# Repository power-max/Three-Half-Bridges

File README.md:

# Three Half Bridges
Three Half Bridges project is intended to be a universal(ish) module for use in larger power conversion and motor control systems. This PCB aims to create a reasonably universal half bridge driver that can be used for medium to high power (100W to 1kW) electrical systems, such as power converters (buck converter, forward converter, LC or LLC converter, etc) motor drivers, etc. As such it is fairly bare-bones and additional components may need to be added external to this PCB for a particular system.

Digital isolator ICs are used for providing isolated gate drive signals and pretty much any generic low-side gate driver can be used for the actual gate driver ICs. I found some cheapies on LCSC for less than a dollar that claim 4A source and sink per channel, and each channel is paralell so in theory 8A source and sink is achievable. Note that there is no logic to prevent shoot-through, as the user inputs each high and low switch independently. Use a TL494 style flip flop based pulse steering network or my Dead Time Insertion PCB to implement this logic from a single ended square wave.

Notes:
The end-user is responsible for selecting the exact componts used for this PCB design. (i.e. MOSFET or IGBT choice, choice of gate driver IC, value of capcitors, etc)

Licensed under the MIT License (https://mit-license.org/)

I was really drunk when I wrote this. Please consider buyin gm e more beerrs so I caan contune edevelopment thnaks!

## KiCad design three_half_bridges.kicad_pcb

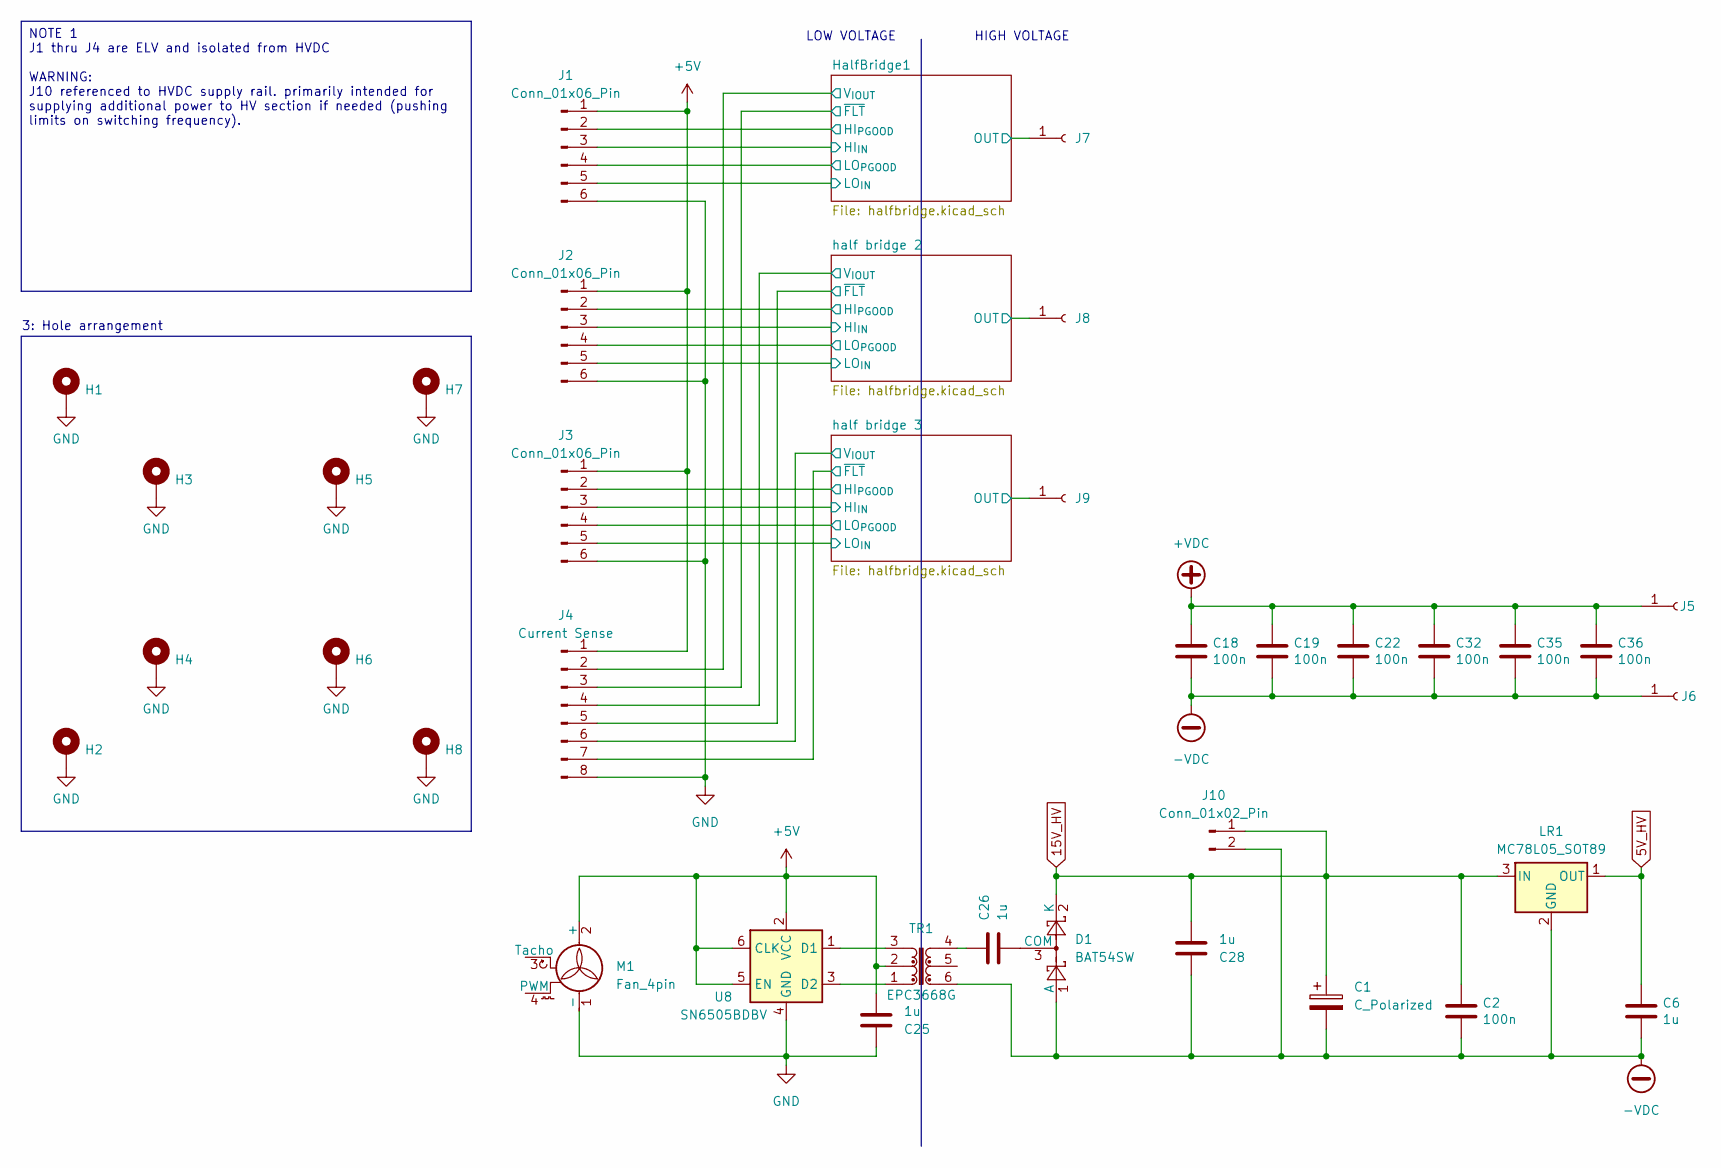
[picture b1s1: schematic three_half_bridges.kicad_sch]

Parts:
C1: C_Polarized; CP_EIA-6032-20_AVX-F
C2: 100n; C_0805_2012Metric
C6: 1u; C_0805_2012Metric
C18, C19, C22, C32, C35, C36: 100n; C_1812_4532Metric
C25, C26, C28: 1u; C_0603_1608Metric
D1: BAT54SW; SOT-323_SC-70
H1, H2, H7, H8: MountingHole_Pad; MountingHole_3.2mm_M3_Pad_Via
H3, H4, H5, H6: MountingHole_Pad; MountingHole_5.5mm_Pad_Via
J1, J2, J3: Conn_01x06_Pin; Molex_PicoBlade_53047-0610_1x06_P1.25mm_Vertical
J4: Current Sense; Molex_PicoBlade_53047-0810_1x08_P1.25mm_Vertical
J5, J6, J7, J8, J9: Conn_01x01_Socket; AMT0450028DB0000G
J10: Conn_01x02_Pin; JST_XH_B2B-XH-A_1x02_P2.50mm_Vertical
LR1: MC78L05_SOT89; SOT-89-3
M1: Fan_4pin; Molex_KK-254_AE-6410-04A_1x04_P2.54mm_Vertical
TR1: EPC3668G; Pulse_PA2004NL
U8: SN6505BDBV; SOT-23-6

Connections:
5V_HV: C6.2, LR1.1 (OUT); also elsewhere on the board
15V_HV: C1.1, C2.2, C28.2, D1.2 (K), J10.1, LR1.3 (IN); also elsewhere on the board
+5V: C25.2, J1.1, J2.1, J3.1, J4.1, M1.2 (+), TR1.2, U8.2 (VCC), U8.5 (EN), U8.6 (CLK); also elsewhere on the board
+VDC: C18.2, C19.2, C22.2, C32.2, C35.2, C36.2, J5.1; also elsewhere on the board
-VDC: C1.2, C2.1, C6.1, C18.1, C19.1, C22.1, C28.1, C32.1, C35.1, C36.1, D1.1 (A), J6.1, J10.2, LR1.2 (GND), TR1.6; also elsewhere on the board
/half bridge 1/HI_{IN}: J1.3; also elsewhere on the board
/half bridge 1/HI_{PGOOD}: J1.2; also elsewhere on the board
/half bridge 1/LO_{IN}: J1.5; also elsewhere on the board
/half bridge 1/LO_{PGOOD}: J1.4; also elsewhere on the board
/half bridge 1/OUT: J7.1; also elsewhere on the board
/half bridge 1/V_{IOUT}: J4.2; also elsewhere on the board
/half bridge 1/~FLT: J4.3; also elsewhere on the board
/half bridge 2/HI_{IN}: J2.3; also elsewhere on the board
/half bridge 2/HI_{PGOOD}: J2.2; also elsewhere on the board
/half bridge 2/LO_{IN}: J2.5; also elsewhere on the board
/half bridge 2/LO_{PGOOD}: J2.4; also elsewhere on the board
/half bridge 2/OUT: J8.1; also elsewhere on the board
/half bridge 2/V_{IOUT}: J4.4; also elsewhere on the board
/half bridge 2/~FLT: J4.5; also elsewhere on the board
/half bridge 3/HI_{IN}: J3.3; also elsewhere on the board
/half bridge 3/HI_{PGOOD}: J3.2; also elsewhere on the board
/half bridge 3/LO_{IN}: J3.5; also elsewhere on the board
/half bridge 3/LO_{PGOOD}: J3.4; also elsewhere on the board
/half bridge 3/OUT: J9.1; also elsewhere on the board
/half bridge 3/V_{IOUT}: J4.6; also elsewhere on the board
/half bridge 3/~FLT: J4.7; also elsewhere on the board
GND: C25.1, H1.1, H2.1, H3.1, H4.1, H5.1, H6.1, H7.1, H8.1, J1.6, J2.6, J3.6, J4.8, M1.1 (-), U8.4 (GND); also elsewhere on the board
unnamed: C26.1, TR1.4
unnamed: C26.2, D1.3 (COM)
unnamed: TR1.3, U8.1 (D1)
unnamed: TR1.1, U8.3 (D2)

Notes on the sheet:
LOW VOLTAGE
HIGH VOLTAGE
3: Hole arrangement
NOTE 1 J1 thru J4 are ELV and isolated from HVDC WARNING: J10 referenced to HVDC supply rail. primarily intended for supplying additional power to HV section if needed (pushing limits on switching frequency).

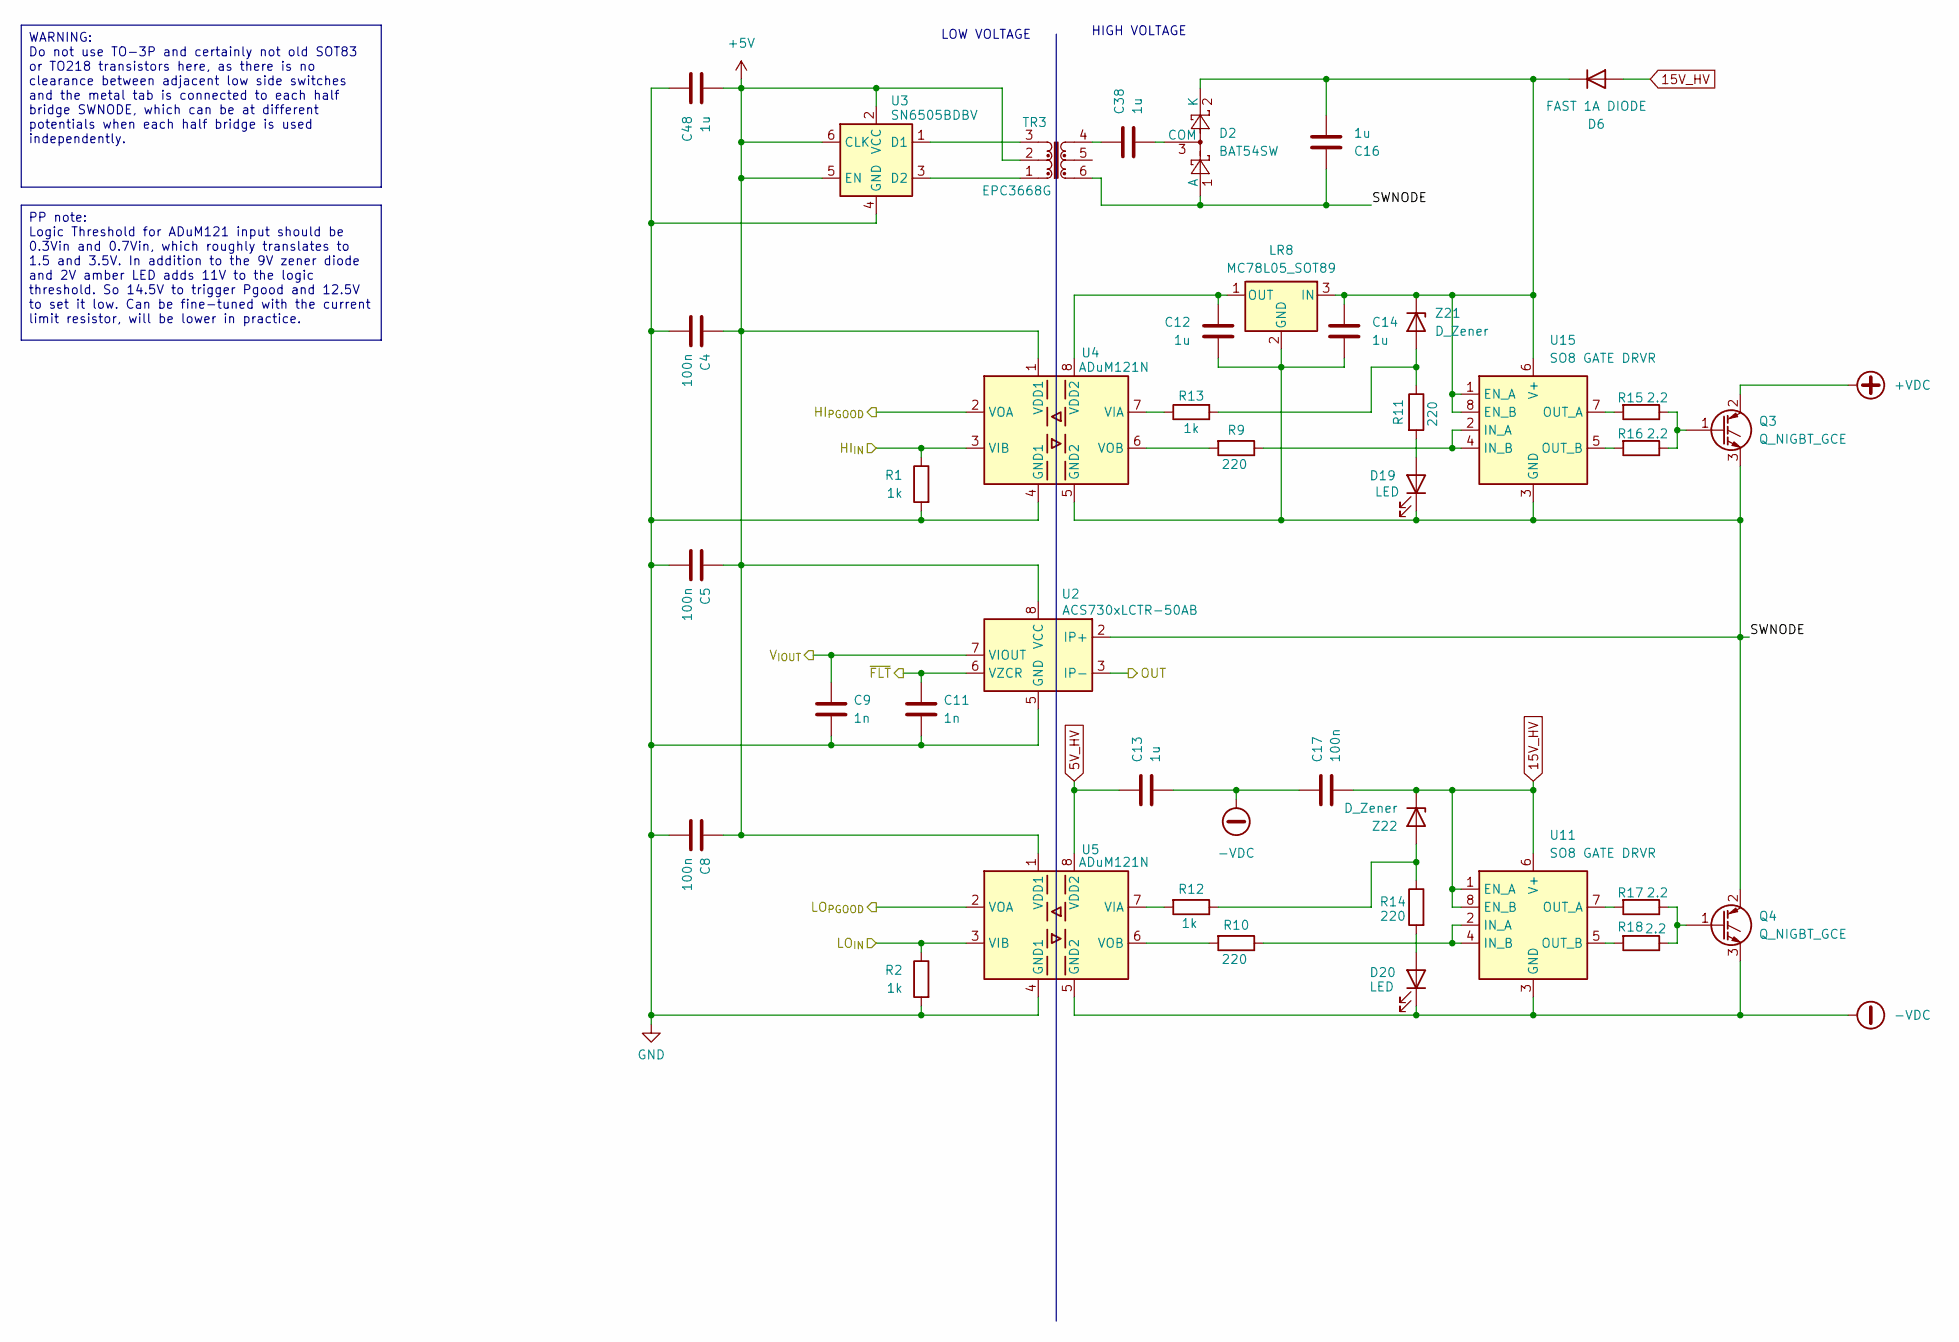
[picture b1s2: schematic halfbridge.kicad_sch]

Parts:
C4, C5, C8, C17: 100n; C_0603_1608Metric
C9, C11: 1n; C_0603_1608Metric
C12, C13, C14, C16, C38, C48: 1u; C_0603_1608Metric
D2: BAT54SW; SOT-323_SC-70
D6: FAST 1A DIODE; D_SOD-128
D19, D20: LED; LED_0805_2012Metric
LR8: MC78L05_SOT89; SOT-89-3
Q3, Q4: Q_NIGBT_GCE; TO-247-3-Nogloryhole_Horizontal_TabUp
R1, R2, R12, R13: 1k; R_0603_1608Metric
R9, R10, R11, R14: 220; R_0603_1608Metric
R15, R16, R17, R18: 2.2; R_1206_3216Metric
TR3: EPC3668G; Pulse_PA2004NL
U2: ACS730xLCTR-50AB; SOIC-8_3.9x4.9mm_P1.27mm
U3: SN6505BDBV; SOT-23-6
U4, U5: ADuM121N; SOIC-8_3.9x4.9mm_P1.27mm
U11, U15: SO8 GATE DRVR; SO-8_3.9x4.9mm_P1.27mm
Z21, Z22: D_Zener; D_SOD-123

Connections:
5V_HV: C13.1, U5.8 (VDD2); also elsewhere on the board
15V_HV: C17.2, D6.2 (A), U11.1 (EN_A), U11.6 (V+), U11.8 (EN_B), Z22.1 (K); also elsewhere on the board
+5V: C4.1, C5.1, C8.1, C48.2, TR3.2, U2.8 (VCC), U3.2 (VCC), U3.5 (EN), U3.6 (CLK), U4.1 (VDD1), U5.1 (VDD1); also elsewhere on the board
+VDC: Q3.2 (C); also elsewhere on the board
-VDC: C13.2, C17.1, D20.1 (K), Q4.3 (E), U5.5 (GND2), U11.3 (GND); also elsewhere on the board
/half bridge 2/HI_{IN}: R1.1, U4.3 (VIB); also elsewhere on the board
/half bridge 2/HI_{PGOOD}: U4.2 (VOA); also elsewhere on the board
/half bridge 2/LO_{IN}: R2.1, U5.3 (VIB); also elsewhere on the board
/half bridge 2/LO_{PGOOD}: U5.2 (VOA); also elsewhere on the board
/half bridge 2/OUT: U2.3 (IP-), U2.4 (IP-); also elsewhere on the board
/half bridge 2/SWNODE: C12.2, C14.2, C16.1, D2.1 (A), D19.1 (K), LR8.2 (GND), Q3.3 (E), Q4.2 (C), TR3.6, U2.1 (IP+), U2.2 (IP+), U4.5 (GND2), U15.3 (GND)
/half bridge 2/V_{IOUT}: C9.1, U2.7 (VIOUT); also elsewhere on the board
/half bridge 2/~FLT: C11.1, U2.6 (VZCR); also elsewhere on the board
GND: C4.2, C5.2, C8.2, C9.2, C11.2, C48.1, R1.2, R2.2, U2.5 (GND), U3.4 (GND), U4.4 (GND1), U5.4 (GND1); also elsewhere on the board
unnamed: C38.1, TR3.4
unnamed: C38.2, D2.3 (COM)
unnamed: C14.1, C16.2, D2.2 (K), D6.1 (K), LR8.3 (IN), U15.1 (EN_A), U15.6 (V+), U15.8 (EN_B), Z21.1 (K)
unnamed: D19.2 (A), R11.2
unnamed: D20.2 (A), R14.2
unnamed: C12.1, LR8.1 (OUT), U4.8 (VDD2)
unnamed: Q3.1 (G), R15.1, R16.1
unnamed: Q4.1 (G), R17.1, R18.1
unnamed: TR3.3, U3.1 (D1)
unnamed: TR3.1, U3.3 (D2)
unnamed: R13.1, U4.7 (VIA)
unnamed: R9.2, U4.6 (VOB)
unnamed: R12.2, U5.7 (VIA)
unnamed: R10.2, U5.6 (VOB)
unnamed: R10.1, U11.2 (IN_A), U11.4 (IN_B)
unnamed: R17.2, U11.7 (OUT_A)
unnamed: R18.2, U11.5 (OUT_B)
unnamed: R9.1, U15.2 (IN_A), U15.4 (IN_B)
unnamed: R15.2, U15.7 (OUT_A)
unnamed: R16.2, U15.5 (OUT_B)
unnamed: R11.1, R13.2, Z21.2 (A)
unnamed: R12.1, R14.1, Z22.2 (A)

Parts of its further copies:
C3, C20, C21, C31, C42, C43, C44, C52: 100n; C_0603_1608Metric
C7, C10, C45, C46: 1n; C_0603_1608Metric
C15, C23, C24, C27, C30, C39, C41, C47, C49, C50, C51, C53: 1u; C_0603_1608Metric
D3, D4: BAT54SW; SOT-323_SC-70
D7, D8: FAST 1A DIODE; D_SOD-128
D9, D10, D30, D31: LED; LED_0805_2012Metric
LR11, LR12: MC78L05_SOT89; SOT-89-3
Q5, Q6, Q7, Q8: Q_NIGBT_GCE; TO-247-3-Nogloryhole_Horizontal_TabUp
R19, R20, R28, R29, R35, R36, R44, R45: 1k; R_0603_1608Metric
R25, R26, R27, R30, R41, R42, R43, R46: 220; R_0603_1608Metric
R31, R32, R33, R34, R47, R48, R49, R50: 2.2; R_1206_3216Metric
TR2, TR4: EPC3668G; Pulse_PA2004NL
U1, U17: ACS730xLCTR-50AB; SOIC-8_3.9x4.9mm_P1.27mm
U6, U7: SN6505BDBV; SOT-23-6
U9, U10, U18, U19: ADuM121N; SOIC-8_3.9x4.9mm_P1.27mm
U12, U13, U14, U22: SO8 GATE DRVR; SO-8_3.9x4.9mm_P1.27mm
Z1, Z2, Z32, Z33: D_Zener; D_SOD-123

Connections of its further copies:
5V_HV: C15.1, C24.1, U10.8 (VDD2), U19.8 (VDD2); also elsewhere on the board
15V_HV: C31.2, C52.2, D7.2 (A), D8.2 (A), U12.1 (EN_A), U12.6 (V+), U12.8 (EN_B), U14.1 (EN_A), U14.6 (V+), U14.8 (EN_B), Z2.1 (K), Z33.1 (K); also elsewhere on the board
+5V: C3.1, C20.1, C21.1, C42.1, C43.1, C44.1, C50.2, C53.2, TR2.2, TR4.2, U1.8 (VCC), U6.2 (VCC), U6.5 (EN), U6.6 (CLK), U7.2 (VCC), U7.5 (EN), U7.6 (CLK), U9.1 (VDD1), U10.1 (VDD1), U17.8 (VCC), U18.1 (VDD1), U19.1 (VDD1); also elsewhere on the board
+VDC: Q5.2 (C), Q7.2 (C); also elsewhere on the board
-VDC: C15.2, C24.2, C31.1, C52.1, D10.1 (K), D31.1 (K), Q6.3 (E), Q8.3 (E), U10.5 (GND2), U12.3 (GND), U14.3 (GND), U19.5 (GND2); also elsewhere on the board
/half bridge 1/HI_{IN}: R19.1, U9.3 (VIB); also elsewhere on the board
/half bridge 1/HI_{PGOOD}: U9.2 (VOA); also elsewhere on the board
/half bridge 1/LO_{IN}: R20.1, U10.3 (VIB); also elsewhere on the board
/half bridge 1/LO_{PGOOD}: U10.2 (VOA); also elsewhere on the board
/half bridge 1/OUT: U17.3 (IP-), U17.4 (IP-); also elsewhere on the board
/half bridge 1/SWNODE: C23.2, C27.2, C30.1, D3.1 (A), D9.1 (K), LR11.2 (GND), Q5.3 (E), Q6.2 (C), TR2.6, U9.5 (GND2), U13.3 (GND), U17.1 (IP+), U17.2 (IP+)
/half bridge 1/V_{IOUT}: C10.1, U17.7 (VIOUT); also elsewhere on the board
/half bridge 1/~FLT: C7.1, U17.6 (VZCR); also elsewhere on the board
/half bridge 3/HI_{IN}: R35.1, U18.3 (VIB); also elsewhere on the board
/half bridge 3/HI_{PGOOD}: U18.2 (VOA); also elsewhere on the board
/half bridge 3/LO_{IN}: R36.1, U19.3 (VIB); also elsewhere on the board
/half bridge 3/LO_{PGOOD}: U19.2 (VOA); also elsewhere on the board
/half bridge 3/OUT: U1.3 (IP-), U1.4 (IP-); also elsewhere on the board
/half bridge 3/SWNODE: C47.2, C49.2, C51.1, D4.1 (A), D30.1 (K), LR12.2 (GND), Q7.3 (E), Q8.2 (C), TR4.6, U1.1 (IP+), U1.2 (IP+), U18.5 (GND2), U22.3 (GND)
/half bridge 3/V_{IOUT}: C45.1, U1.7 (VIOUT); also elsewhere on the board
/half bridge 3/~FLT: C46.1, U1.6 (VZCR); also elsewhere on the board
GND: C3.2, C7.2, C10.2, C20.2, C21.2, C42.2, C43.2, C44.2, C45.2, C46.2, C50.1, C53.1, R19.2, R20.2, R35.2, R36.2, U1.5 (GND), U6.4 (GND), U7.4 (GND), U9.4 (GND1), U10.4 (GND1), U17.5 (GND), U18.4 (GND1), U19.4 (GND1); also elsewhere on the board
unnamed: C39.1, TR2.4
unnamed: C41.1, TR4.4
unnamed: C39.2, D3.3 (COM)
unnamed: C27.1, C30.2, D3.2 (K), D7.1 (K), LR11.3 (IN), U13.1 (EN_A), U13.6 (V+), U13.8 (EN_B), Z1.1 (K)
unnamed: C41.2, D4.3 (COM)
unnamed: C49.1, C51.2, D4.2 (K), D8.1 (K), LR12.3 (IN), U22.1 (EN_A), U22.6 (V+), U22.8 (EN_B), Z32.1 (K)
unnamed: D9.2 (A), R27.2
unnamed: D10.2 (A), R30.2
unnamed: D30.2 (A), R43.2
unnamed: D31.2 (A), R46.2
unnamed: C23.1, LR11.1 (OUT), U9.8 (VDD2)
unnamed: C47.1, LR12.1 (OUT), U18.8 (VDD2)
unnamed: Q5.1 (G), R31.1, R32.1
unnamed: Q6.1 (G), R33.1, R34.1
unnamed: Q7.1 (G), R47.1, R48.1
unnamed: Q8.1 (G), R49.1, R50.1
unnamed: TR2.3, U6.1 (D1)
unnamed: TR2.1, U6.3 (D2)
unnamed: TR4.3, U7.1 (D1)
unnamed: TR4.1, U7.3 (D2)
unnamed: R29.1, U9.7 (VIA)
unnamed: R25.2, U9.6 (VOB)
unnamed: R28.2, U10.7 (VIA)
unnamed: R26.2, U10.6 (VOB)
unnamed: R26.1, U12.2 (IN_A), U12.4 (IN_B)
unnamed: R33.2, U12.7 (OUT_A)
unnamed: R34.2, U12.5 (OUT_B)
unnamed: R25.1, U13.2 (IN_A), U13.4 (IN_B)
unnamed: R31.2, U13.7 (OUT_A)
unnamed: R32.2, U13.5 (OUT_B)
unnamed: R42.1, U14.2 (IN_A), U14.4 (IN_B)
unnamed: R49.2, U14.7 (OUT_A)
unnamed: R50.2, U14.5 (OUT_B)
unnamed: R45.1, U18.7 (VIA)
unnamed: R41.2, U18.6 (VOB)
unnamed: R44.2, U19.7 (VIA)
unnamed: R42.2, U19.6 (VOB)
unnamed: R41.1, U22.2 (IN_A), U22.4 (IN_B)
unnamed: R47.2, U22.7 (OUT_A)
unnamed: R48.2, U22.5 (OUT_B)
unnamed: R27.1, R29.2, Z1.2 (A)
unnamed: R28.1, R30.1, Z2.2 (A)
unnamed: R43.1, R45.2, Z32.2 (A)
unnamed: R44.1, R46.1, Z33.2 (A)

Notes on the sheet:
HIGH VOLTAGE
LOW VOLTAGE
WARNING: Do not use TO-3P and certainly not old SOT83 or TO218 transistors here, as there is no clearance between adjacent low side switches and the metal tab is connected to each half bridge SWNODE, which can be at different potentials when each half bridge is used independently.
PP note: Logic Threshold for ADuM121 input should be 0.3Vin and 0.7Vin, which roughly translates to 1.5 and 3.5V. In addition to the 9V zener diode and 2V amber LED adds 11V to the logic threshold. So 14.5V to trigger Pgood and 12.5V to set it low. Can be fine-tuned with the current limit resistor,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

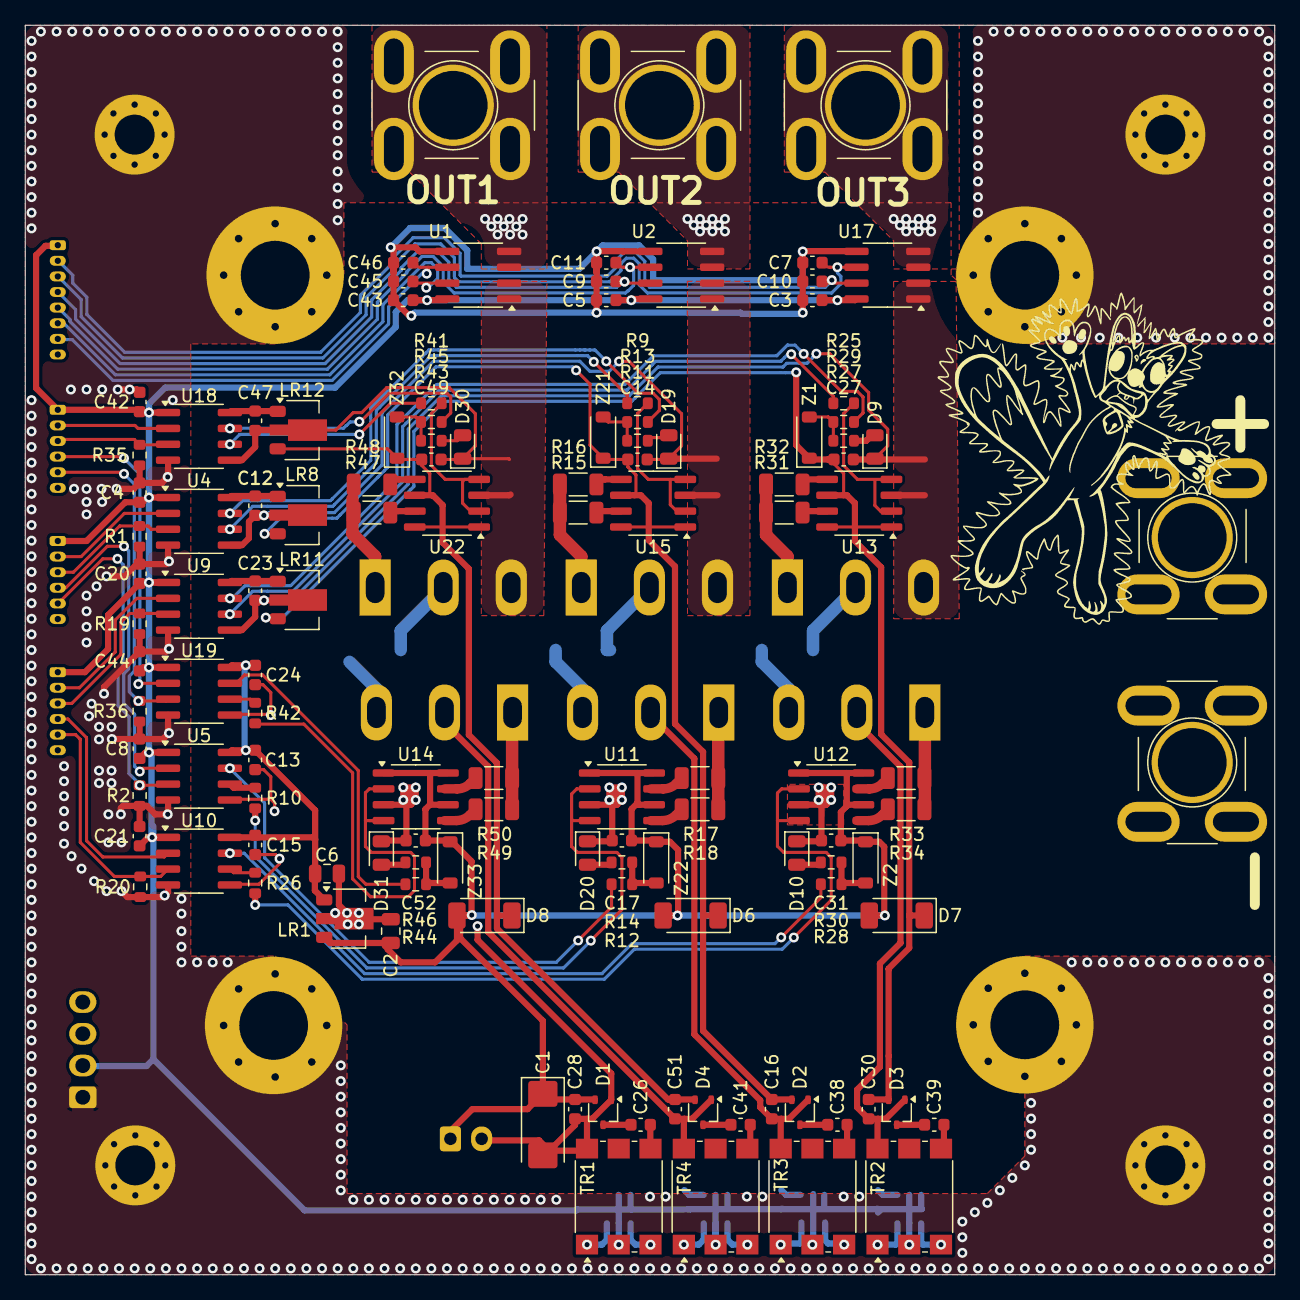
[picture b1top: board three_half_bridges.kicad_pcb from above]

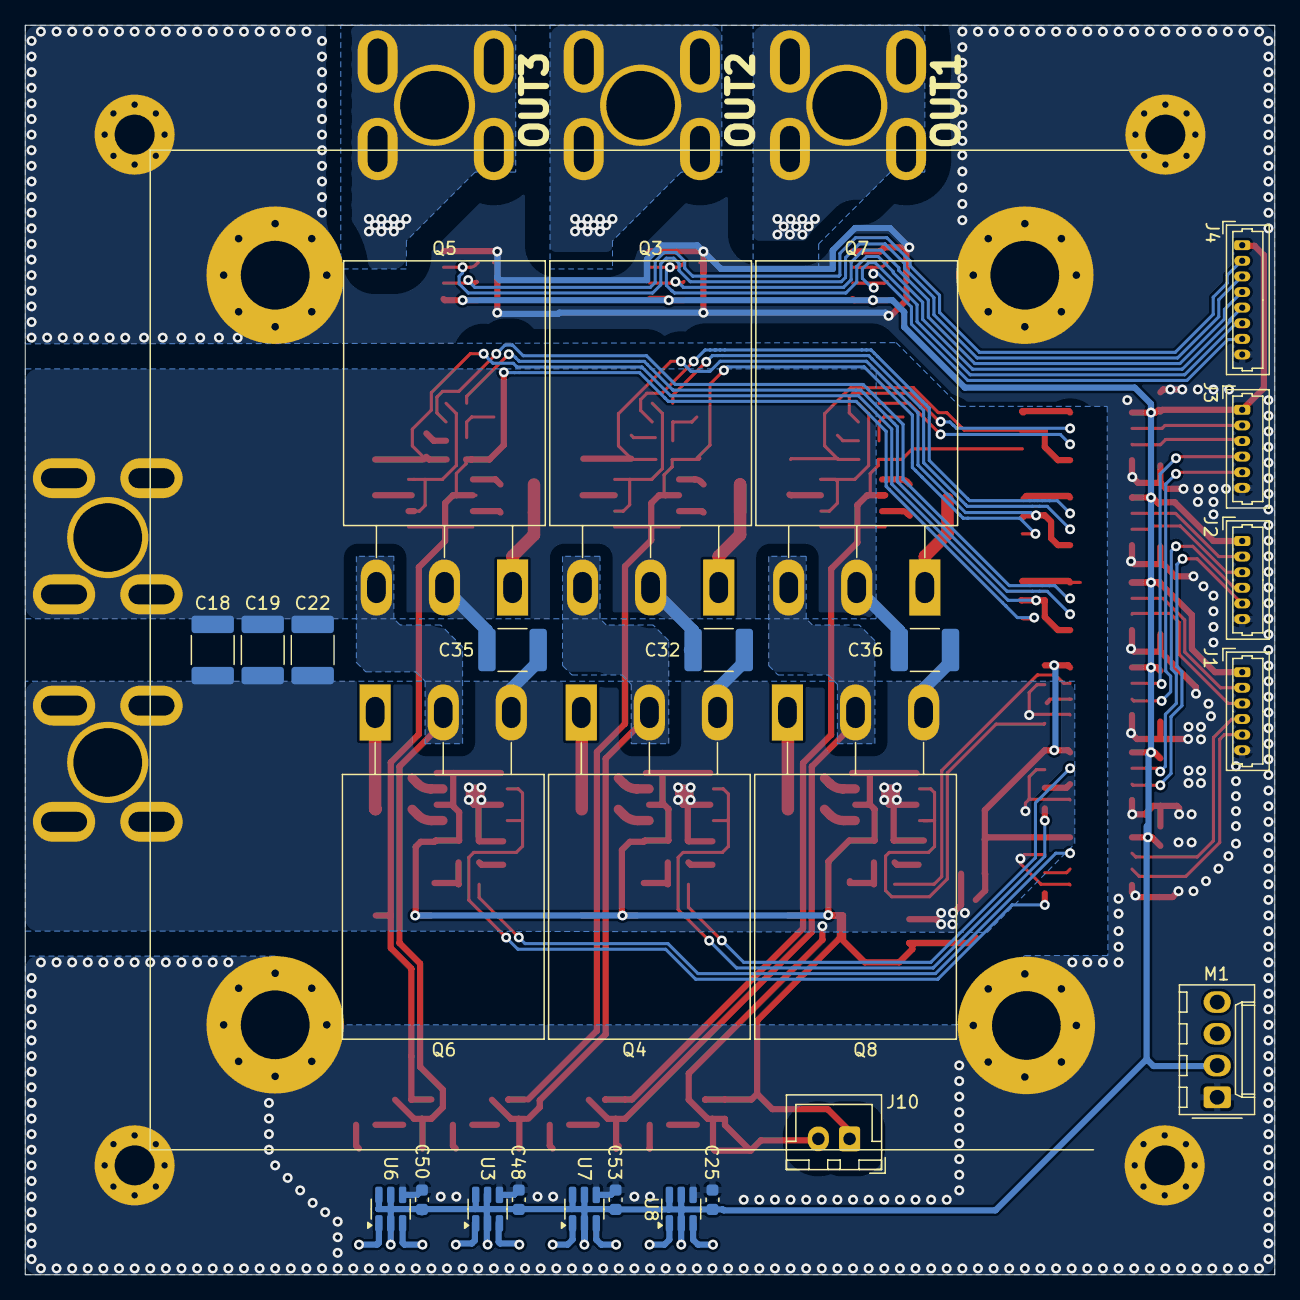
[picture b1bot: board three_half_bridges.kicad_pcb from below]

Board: 4 copper layers, 100.0 x 100.0 mm, 155 parts (26 on the bottom side), 100 nets.

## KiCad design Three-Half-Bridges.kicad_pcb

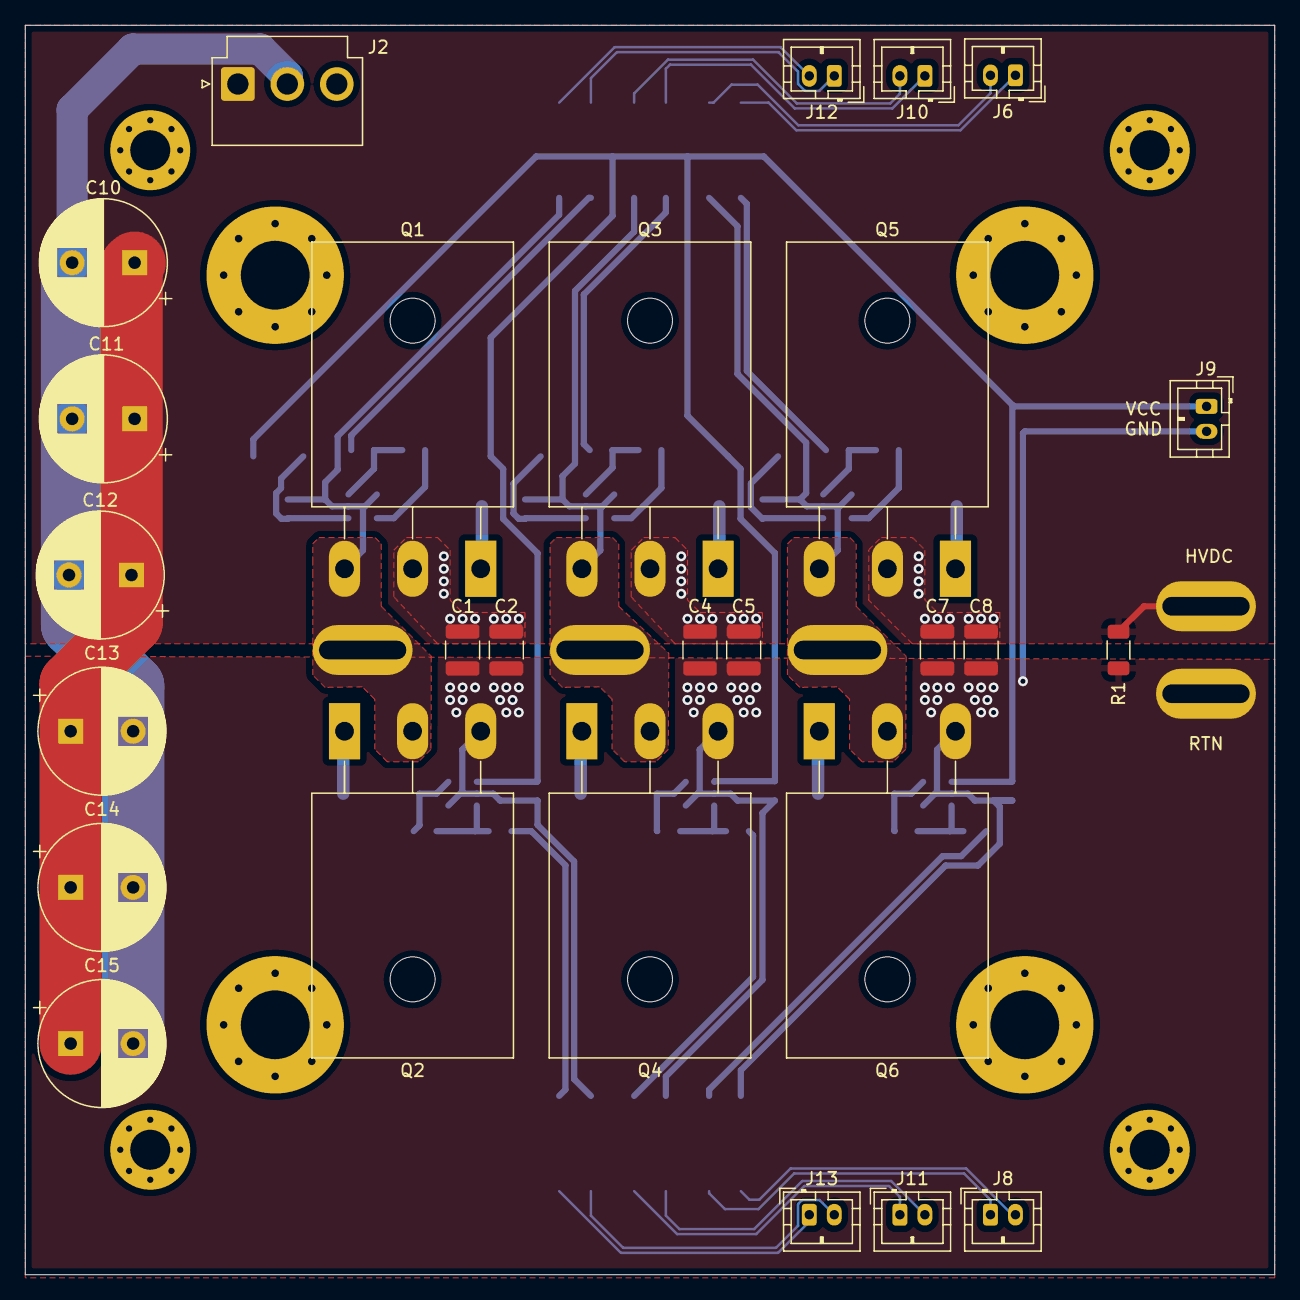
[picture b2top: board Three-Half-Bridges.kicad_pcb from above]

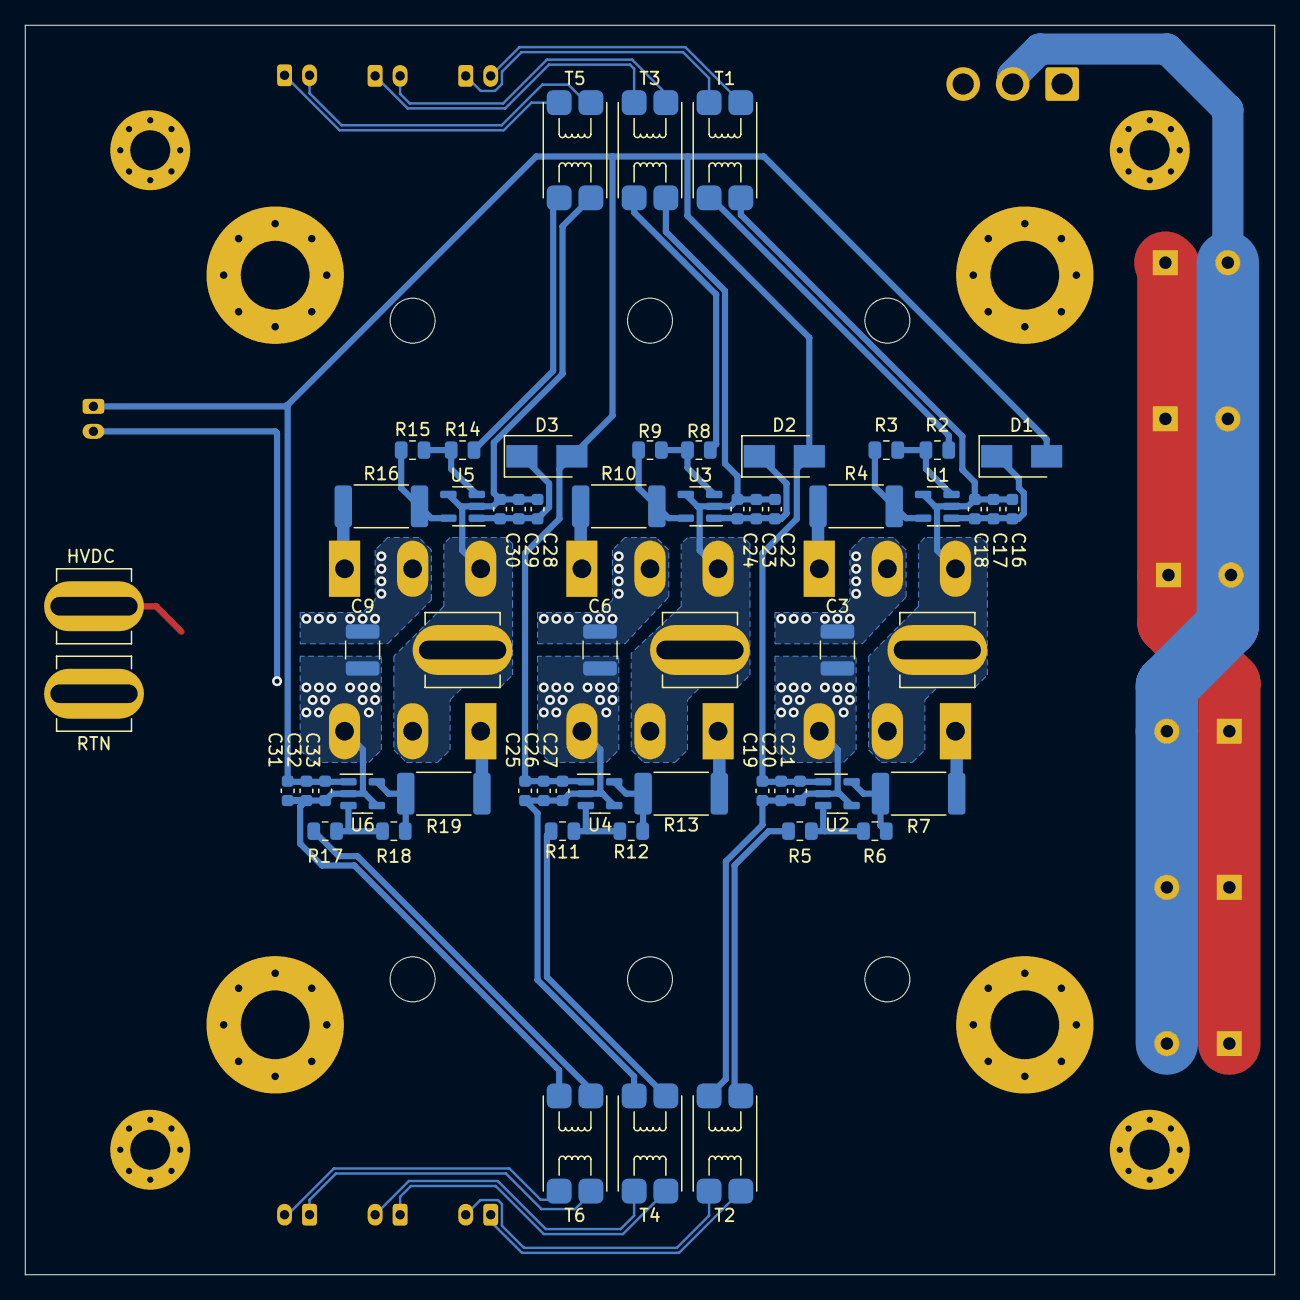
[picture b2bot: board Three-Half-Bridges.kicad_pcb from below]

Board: 2 copper layers, 100.0 x 100.0 mm, 94 parts (63 on the bottom side), 45 nets.

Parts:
C1, C2, C3, C4, C5, C6, C7, C8, C9: 100n; C_1210_3225Metric
C10, C11, C12, C13, C14, C15: 100uF; CP_Radial_D10.0mm_P5.00mm
C16, C17, C19, C20, C22, C23, C25, C26, C28, C29, C31, C32: 100n; C_0603_1608Metric
C18, C21, C24, C27, C30, C33: 10n; C_0603_1608Metric
D1, D2, D3: D; D_SMA
H1, H2, H3, H4: MountingHole_Pad; MountingHole_5.5mm_Pad_Via
H5, H6, H7, H8: MountingHole_Pad; MountingHole_3.2mm_M3_Pad_Via
J1, J3, J4, J5, J7: Conn_01x01_Female; Screw Terminal 1
J2: Conn_01x03_Male; JST_VH_B3P-VH-B_1x03_P3.96mm_Vertical
J6, J8, J9, J10, J11, J12, J13: Conn_01x02_Male; JST_PH_B2B-PH-K_1x02_P2.00mm_Vertical
Q1, Q2, Q3, Q4, Q5, Q6: Q_NMOS_GDS; TO-247-3_Horizontal_TabUp
R1: 1000; R_1206_3216Metric
R2, R3, R5, R6, R8, R9, R11, R12, R14, R15, R17, R18: 5; R_0805_2012Metric
R4, R7, R10, R13, R16, R19: 5; R_2512_6332Metric_Pad1.40x3.35mm_HandSolder
T1, T2, T3, T4, T5, T6: PulseTrans 1:1; ESMIT-4180
U1, U2, U3, U4, U5, U6: UCC27517; SOT-23-5

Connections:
/half_bridge1/IN_H+: J10.1, T3.2 (AB)
/half_bridge1/IN_H-: J10.2, T3.1 (AA)
/half_bridge1/IN_L+: J11.1, T4.2 (AB)
/half_bridge1/IN_L-: J11.2, T4.1 (AA)
/half_bridge1/OUT: C22.1, C23.1, C24.1, J4.1, Q3.3 (S), Q4.2 (D), T3.4 (SB), U3.2 (GND), U3.4 (Vin-)
/half_bridge2/IN_H+: J6.1, T5.2 (AB)
/half_bridge2/IN_H-: J6.2, T5.1 (AA)
/half_bridge2/IN_L+: J8.1, T6.2 (AB)
/half_bridge2/IN_L-: J8.2, T6.1 (AA)
/half_bridge2/OUT: C28.1, C29.1, C30.1, J3.1, Q5.3 (S), Q6.2 (D), T5.4 (SB), U5.2 (GND), U5.4 (Vin-)
/half_bridge/IN_H+: J12.1, T1.2 (AB)
/half_bridge/IN_H-: J12.2, T1.1 (AA)
/half_bridge/IN_L+: J13.1, T2.2 (AB)
/half_bridge/IN_L-: J13.2, T2.1 (AA)
/half_bridge/OUT: C16.1, C17.1, C18.1, J5.1, Q1.3 (S), Q2.2 (D), T1.4 (SB), U1.2 (GND), U1.4 (Vin-)
GND: C1.1, C2.1, C3.1, C4.1, C5.1, C6.1, C7.1, C8.1, C9.1, C10.2, C11.2, C12.2, C13.2, C14.2, C15.2, C19.1, C20.1, C21.1, C25.1, C26.1, C27.1, C31.1, C32.1, C33.1, J2.2, J7.1, J9.2, Q2.3 (S), Q4.3 (S), Q6.3 (S), R1.2, T2.4 (SB), T4.4 (SB), T6.4 (SB), U2.2 (GND), U2.4 (Vin-), U4.2 (GND), U4.4 (Vin-), U6.2 (GND), U6.4 (Vin-)
unnamed: C16.2, C17.2, C18.2, D1.1 (K), U1.1 (VDD)
unnamed: C22.2, C23.2, C24.2, D2.1 (K), U3.1 (VDD)
unnamed: C28.2, C29.2, C30.2, D3.1 (K), U5.1 (VDD)
unnamed: Q1.1 (G), R4.1
unnamed: Q2.1 (G), R7.1
unnamed: Q3.1 (G), R10.1
unnamed: Q4.1 (G), R13.1
unnamed: Q5.1 (G), R16.1
unnamed: Q6.1 (G), R19.1
unnamed: R2.1, R3.2, U1.3 (Vin+)
unnamed: R2.2, T1.3 (SA)
unnamed: R3.1, R4.2, U1.5 (OUT)
unnamed: R5.1, R6.2, U2.3 (Vin+)
unnamed: R5.2, T2.3 (SA)
unnamed: R6.1, R7.2, U2.5 (OUT)
unnamed: R8.1, R9.2, U3.3 (Vin+)
unnamed: R8.2, T3.3 (SA)
unnamed: R9.1, R10.2, U3.5 (OUT)
unnamed: R11.1, R12.2, U4.3 (Vin+)
unnamed: R11.2, T4.3 (SA)
unnamed: R12.1, R13.2, U4.5 (OUT)
unnamed: R14.1, R15.2, U5.3 (Vin+)
unnamed: R14.2, T5.3 (SA)
unnamed: R15.1, R16.2, U5.5 (OUT)
unnamed: R17.1, R18.2, U6.3 (Vin+)
unnamed: R17.2, T6.3 (SA)
unnamed: R18.1, R19.2, U6.5 (OUT)
VBUS: C1.2, C2.2, C3.2, C4.2, C5.2, C6.2, C7.2, C8.2, C9.2, C10.1, C11.1, C12.1, C13.1, C14.1, C15.1, J1.1, J2.1, Q1.2 (D), Q3.2 (D), Q5.2 (D), R1.1
VCC: C19.2, C20.2, C21.2, C25.2, C26.2, C27.2, C31.2, C32.2, C33.2, D1.2 (A), D2.2 (A), D3.2 (A), J9.1, U2.1 (VDD), U4.1 (VDD), U6.1 (VDD)
